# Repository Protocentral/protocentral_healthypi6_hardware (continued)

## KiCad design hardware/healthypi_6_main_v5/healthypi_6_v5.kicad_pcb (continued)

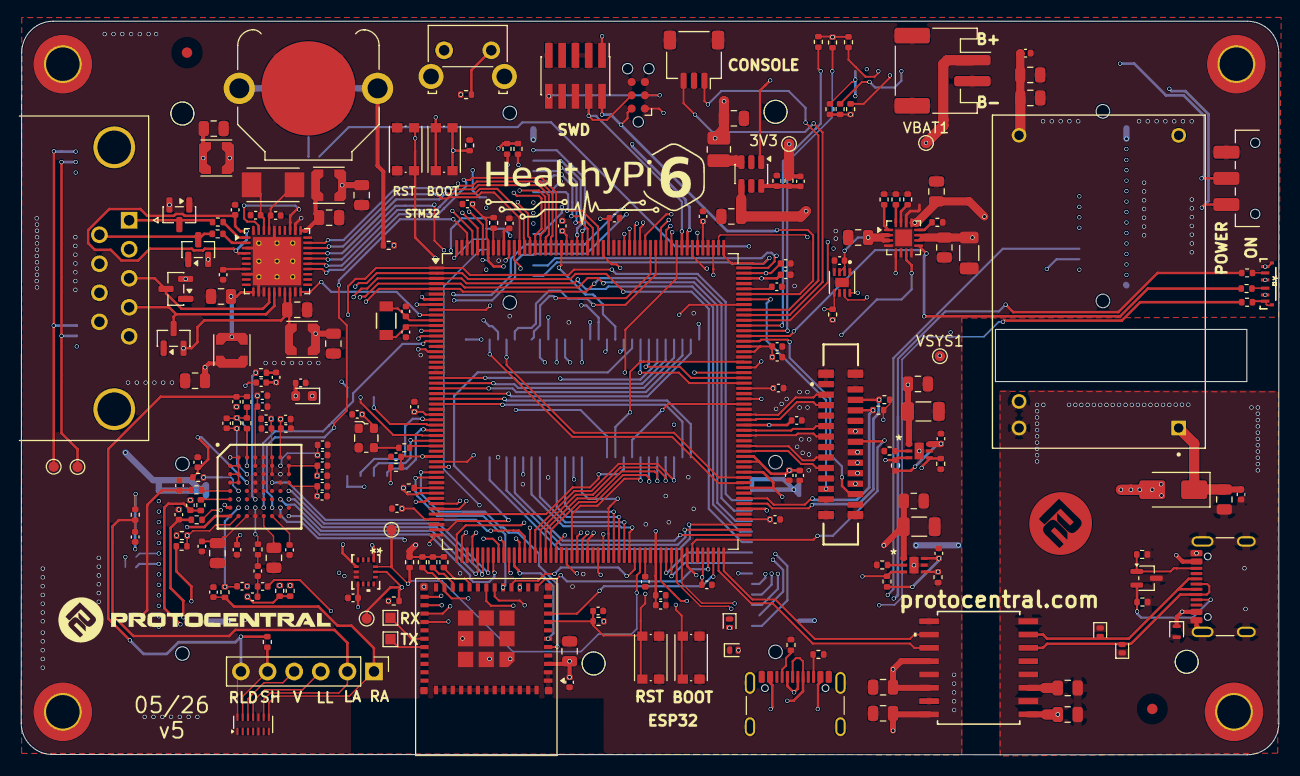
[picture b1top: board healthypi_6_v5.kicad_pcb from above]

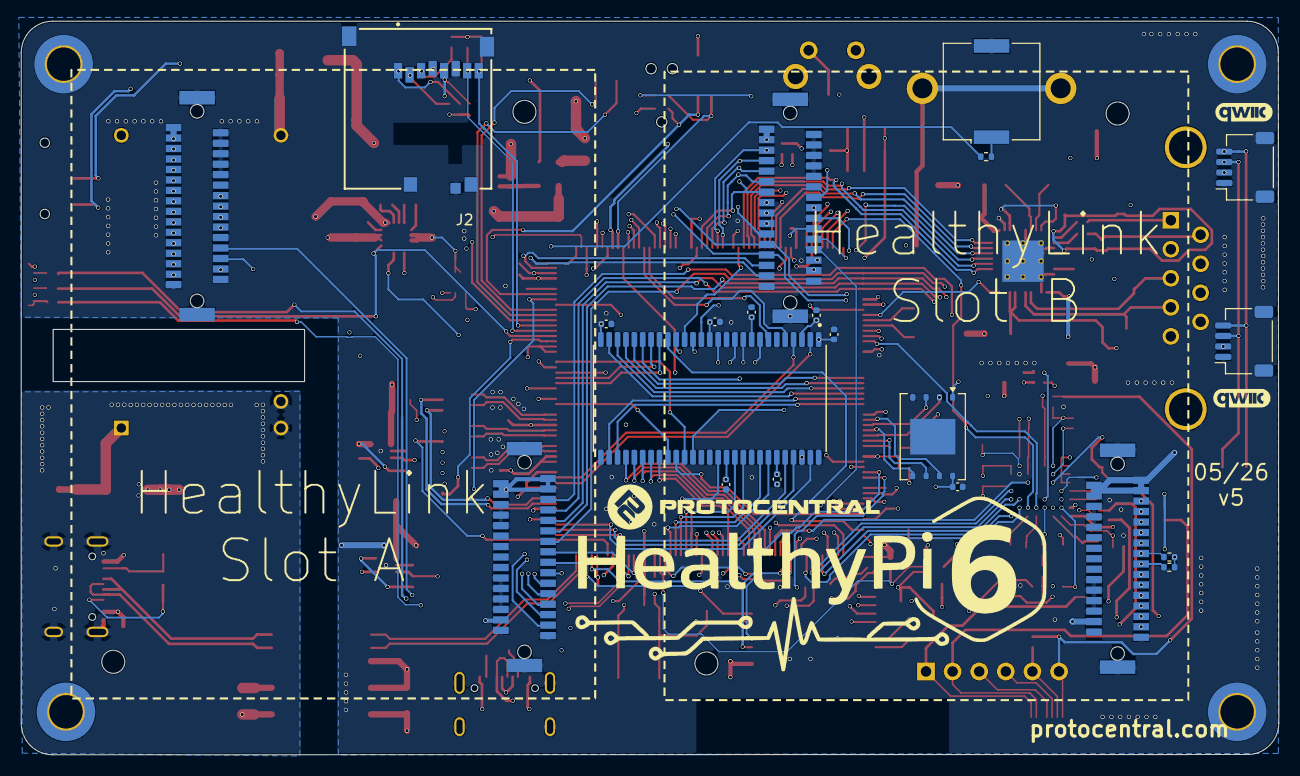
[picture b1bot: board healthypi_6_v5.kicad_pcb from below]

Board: 6 copper layers, 120.0 x 70.0 mm, 240 parts (17 on the bottom side), 241 nets.

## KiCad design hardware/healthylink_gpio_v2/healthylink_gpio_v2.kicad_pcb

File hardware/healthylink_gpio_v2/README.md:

# HealthyLink GPIO Module

| | |
|---|---|
| Revision | **v2** |
| Role | HealthyLink GPIO breakout — the minimal module example |
| Board | 50 × 62.2 mm, 2-layer |
| Slot | Occupies one HealthyLink slot (J5) |
| KiCad | 10 |
| Schematic PDF | [`healthylink-gpio-v2-schematic.pdf`](healthylink-gpio-v2-schematic.pdf) |

## Files

| File | Contents |
|---|---|
| `healthylink_gpio_v2.kicad_pro` / `.kicad_sch` / `.kicad_pcb` | KiCad project for this revision |
| `healthylink-gpio-v2-schematic.pdf` | Exported schematic — the human-readable reference |

## What it does

A single-sheet board that brings the HealthyLink bus out to two 2×10 headers. It is the
smallest complete module in this repository and the recommended starting point for your
own design: it shows the three things every module needs and nothing else.

- **Connector** — one `HEALTHYLINK_DF9_DUAL` (J5), the two DF9-31 receptacles of one slot
- **Identification** — AT24CS02 EEPROM on `I2C3`, with a write-protect solder jumper
- **Power** — a TPS62A02 buck off the module rail

Both SPI buses, `I2C3`, `USART2`, the six analog inputs, CAN, the stacking bus and the
per-slot interrupt and reset all reach the headers. See
[`docs/HEALTHYLINK.md`](../../docs/HEALTHYLINK.md) for the pinout.

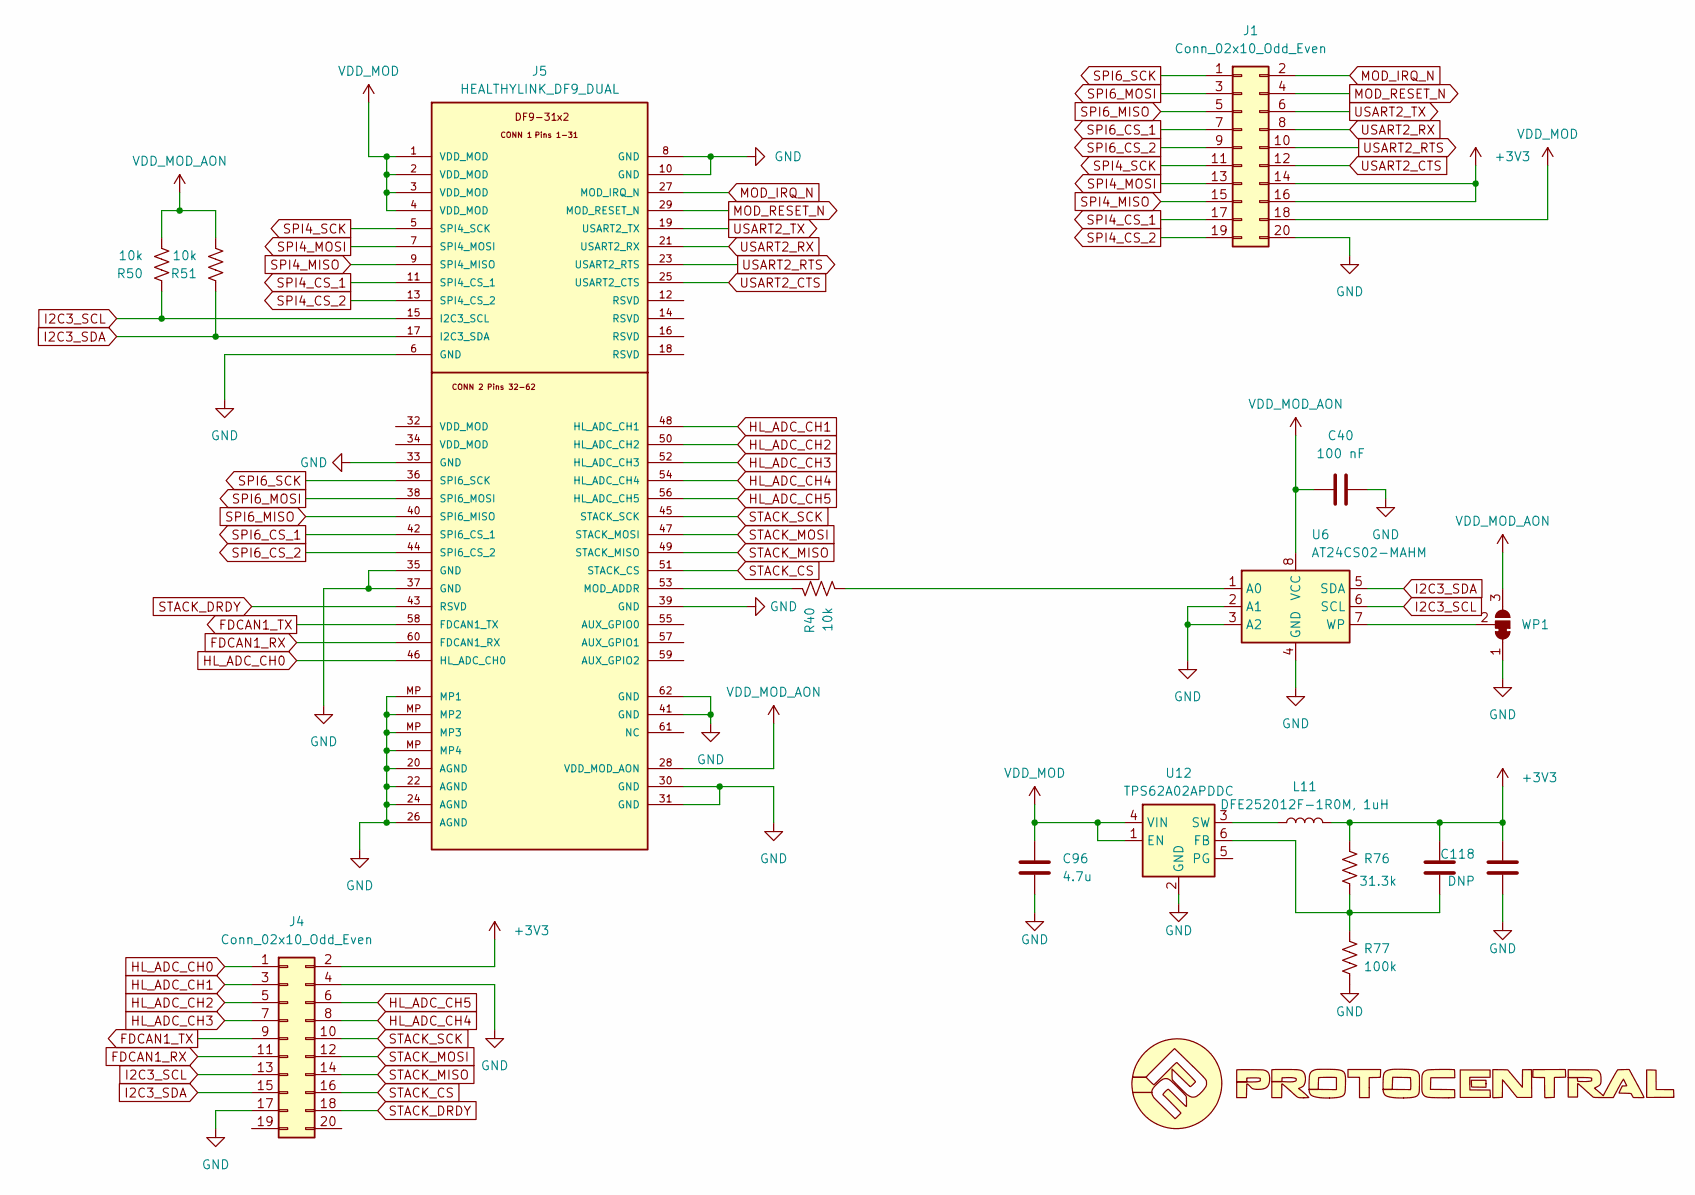
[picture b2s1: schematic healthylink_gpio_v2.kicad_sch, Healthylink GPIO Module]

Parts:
C40: 100 nF; C_0402_1005Metric
C96: 4.7u; C_0805_2012Metric
C118: DNP; C_0402_1005Metric
C119: 22u; C_0805_2012Metric
J1, J4: Conn_02x10_Odd_Even; PinSocket_2x10_P2.54mm_Horizontal
J5: HEALTHYLINK_DF9_DUAL; healthylink_df9_module
L11: DFE252012F-1R0M, 1uH; L_1008_2520Metric
R40, R50, R51: 10k; R_0402_1005Metric
R76: 31.3k; R_0402_1005Metric
R77: 100k; R_0402_1005Metric
U4: LOGO
U6: AT24CS02-MAHM; DFN-8-1EP_3x2mm_P0.5mm_EP1.3x1.5mm
U12: TPS62A02APDDC; SOT-23-6
WP1: SolderJumper_3_Bridged12; SolderJumper-3_P1.3mm_Bridged12_RoundedPad1.0x1.5mm

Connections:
+3V3: C118.2, C119.1, J1.14, J1.16, J4.2, L11.2, R76.2
FDCAN1_RX: J4.11, J5.60 (FDCAN1_RX)
FDCAN1_TX: J4.9, J5.58 (FDCAN1_TX)
GND: C40.1, C96.2, C119.2, J1.20, J4.4, J4.17, J5.6 (GND), J5.8 (GND), J5.10 (GND), J5.20 (AGND), J5.22 (AGND), J5.24 (AGND), J5.26 (AGND), J5.30 (GND), J5.31 (GND), J5.33 (GND), J5.35 (GND), J5.37 (GND), J5.39 (GND), J5.41 (GND), J5.62 (GND), J5.MP (MP1), R77.1, U6.2 (A1), U6.3 (A2), U6.4 (GND), U6.9 (GND), U12.2 (GND), WP1.1 (A)
HL_ADC_CH0: J4.1, J5.46 (HL_ADC_CH0)
HL_ADC_CH1: J4.3, J5.48 (HL_ADC_CH1)
HL_ADC_CH2: J4.5, J5.50 (HL_ADC_CH2)
HL_ADC_CH3: J4.7, J5.52 (HL_ADC_CH3)
HL_ADC_CH4: J4.8, J5.54 (HL_ADC_CH4)
HL_ADC_CH5: J4.6, J5.56 (HL_ADC_CH5)
I2C3_SCL: J4.13, J5.15 (I2C3_SCL), R50.1, U6.6 (SCL)
I2C3_SDA: J4.15, J5.17 (I2C3_SDA), R51.1, U6.5 (SDA)
MOD_IRQ_N: J1.2, J5.27 (MOD_IRQ_N)
MOD_RESET_N: J1.4, J5.29 (MOD_RESET_N)
unnamed: J5.53 (MOD_ADDR), R40.1
unnamed: R40.2, U6.1 (A0)
unnamed: U6.7 (WP), WP1.2 (C)
unnamed: C118.1, R76.1, R77.2, U12.6 (FB)
unnamed: L11.1, U12.3 (SW)
SPI4_CS_1: J1.17, J5.11 (SPI4_CS_1)
SPI4_CS_2: J1.19, J5.13 (SPI4_CS_2)
SPI4_MISO: J1.15, J5.9 (SPI4_MISO)
SPI4_MOSI: J1.13, J5.7 (SPI4_MOSI)
SPI4_SCK: J1.11, J5.5 (SPI4_SCK)
SPI6_CS_1: J1.7, J5.42 (SPI6_CS_1)
SPI6_CS_2: J1.9, J5.44 (SPI6_CS_2)
SPI6_MISO: J1.5, J5.40 (SPI6_MISO)
SPI6_MOSI: J1.3, J5.38 (SPI6_MOSI)
SPI6_SCK: J1.1, J5.36 (SPI6_SCK)
STACK_CS: J4.16, J5.51 (STACK_CS)
STACK_DRDY: J4.18, J5.43 (RSVD)
STACK_MISO: J4.14, J5.49 (STACK_MISO)
STACK_MOSI: J4.12, J5.47 (STACK_MOSI)
STACK_SCK: J4.10, J5.45 (STACK_SCK)
USART2_CTS: J1.12, J5.25 (USART2_CTS)
USART2_RTS: J1.10, J5.23 (USART2_RTS)
USART2_RX: J1.8, J5.21 (USART2_RX)
USART2_TX: J1.6, J5.19 (USART2_TX)
VDD_MOD: C96.1, J1.18, J5.1 (VDD_MOD), J5.2 (VDD_MOD), J5.3 (VDD_MOD), J5.4 (VDD_MOD), U12.1 (EN), U12.4 (VIN)
VDD_MOD_AON: C40.2, J5.28 (VDD_MOD_AON), R50.2, R51.2, U6.8 (VCC), WP1.3 (B)

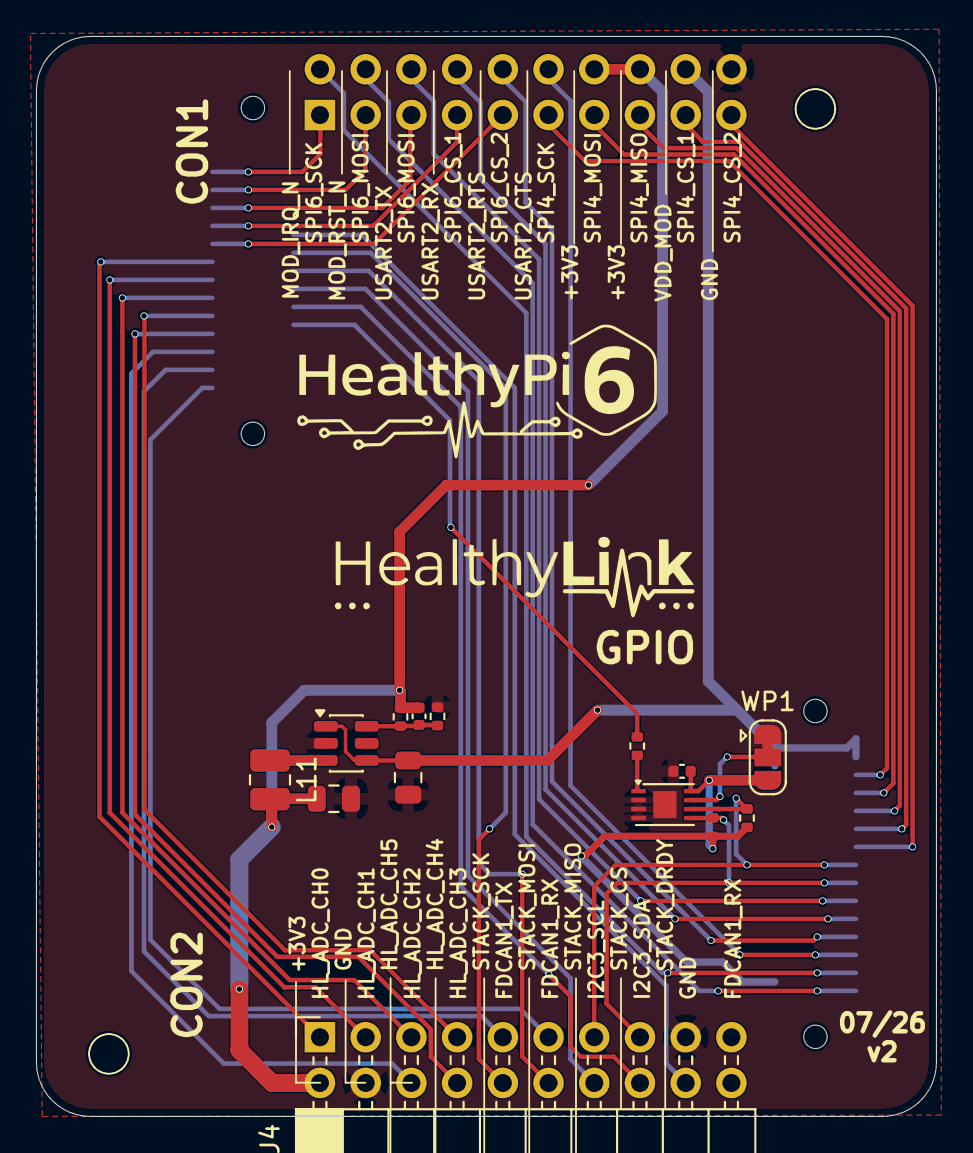
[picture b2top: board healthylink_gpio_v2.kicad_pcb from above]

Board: 2 copper layers, 50.0 x 60.0 mm, 16 parts (1 on the bottom side), 40 nets.

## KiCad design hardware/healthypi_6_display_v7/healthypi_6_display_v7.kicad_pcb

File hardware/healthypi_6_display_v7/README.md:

# HealthyPi 6 Display Board

| | |
|---|---|
| Revision | **v7** |
| Role | Display interface — routes MIPI-DSI and touch I²C from the main board to the 4" panel, and drives the backlight |
| Board | 60 × 33 mm, 2-layer |
| KiCad | 10 |
| Schematic PDF | [`healthypi6-display-v7-schematic.pdf`](healthypi6-display-v7-schematic.pdf) |

## Files

| File | Contents |
|---|---|
| `healthypi_6_display_v7.kicad_pro` / `.kicad_sch` / `.kicad_pcb` | KiCad project for this revision |
| `healthypi6-display-v7-schematic.pdf` | Exported schematic — the human-readable reference |

## Interfaces

- 24-way FFC to the main board: 2-lane MIPI-DSI, touch I²C (`TP_SCL` / `TP_SDA`,
  `TP_INT`, `TP_RST`), panel reset and tearing-effect (`MIPI_RST`, `MIPI_TE`)
- TPS61158 boost driving the panel backlight, enabled by `MIPI_BKL`
- 12-way connector to the display panel

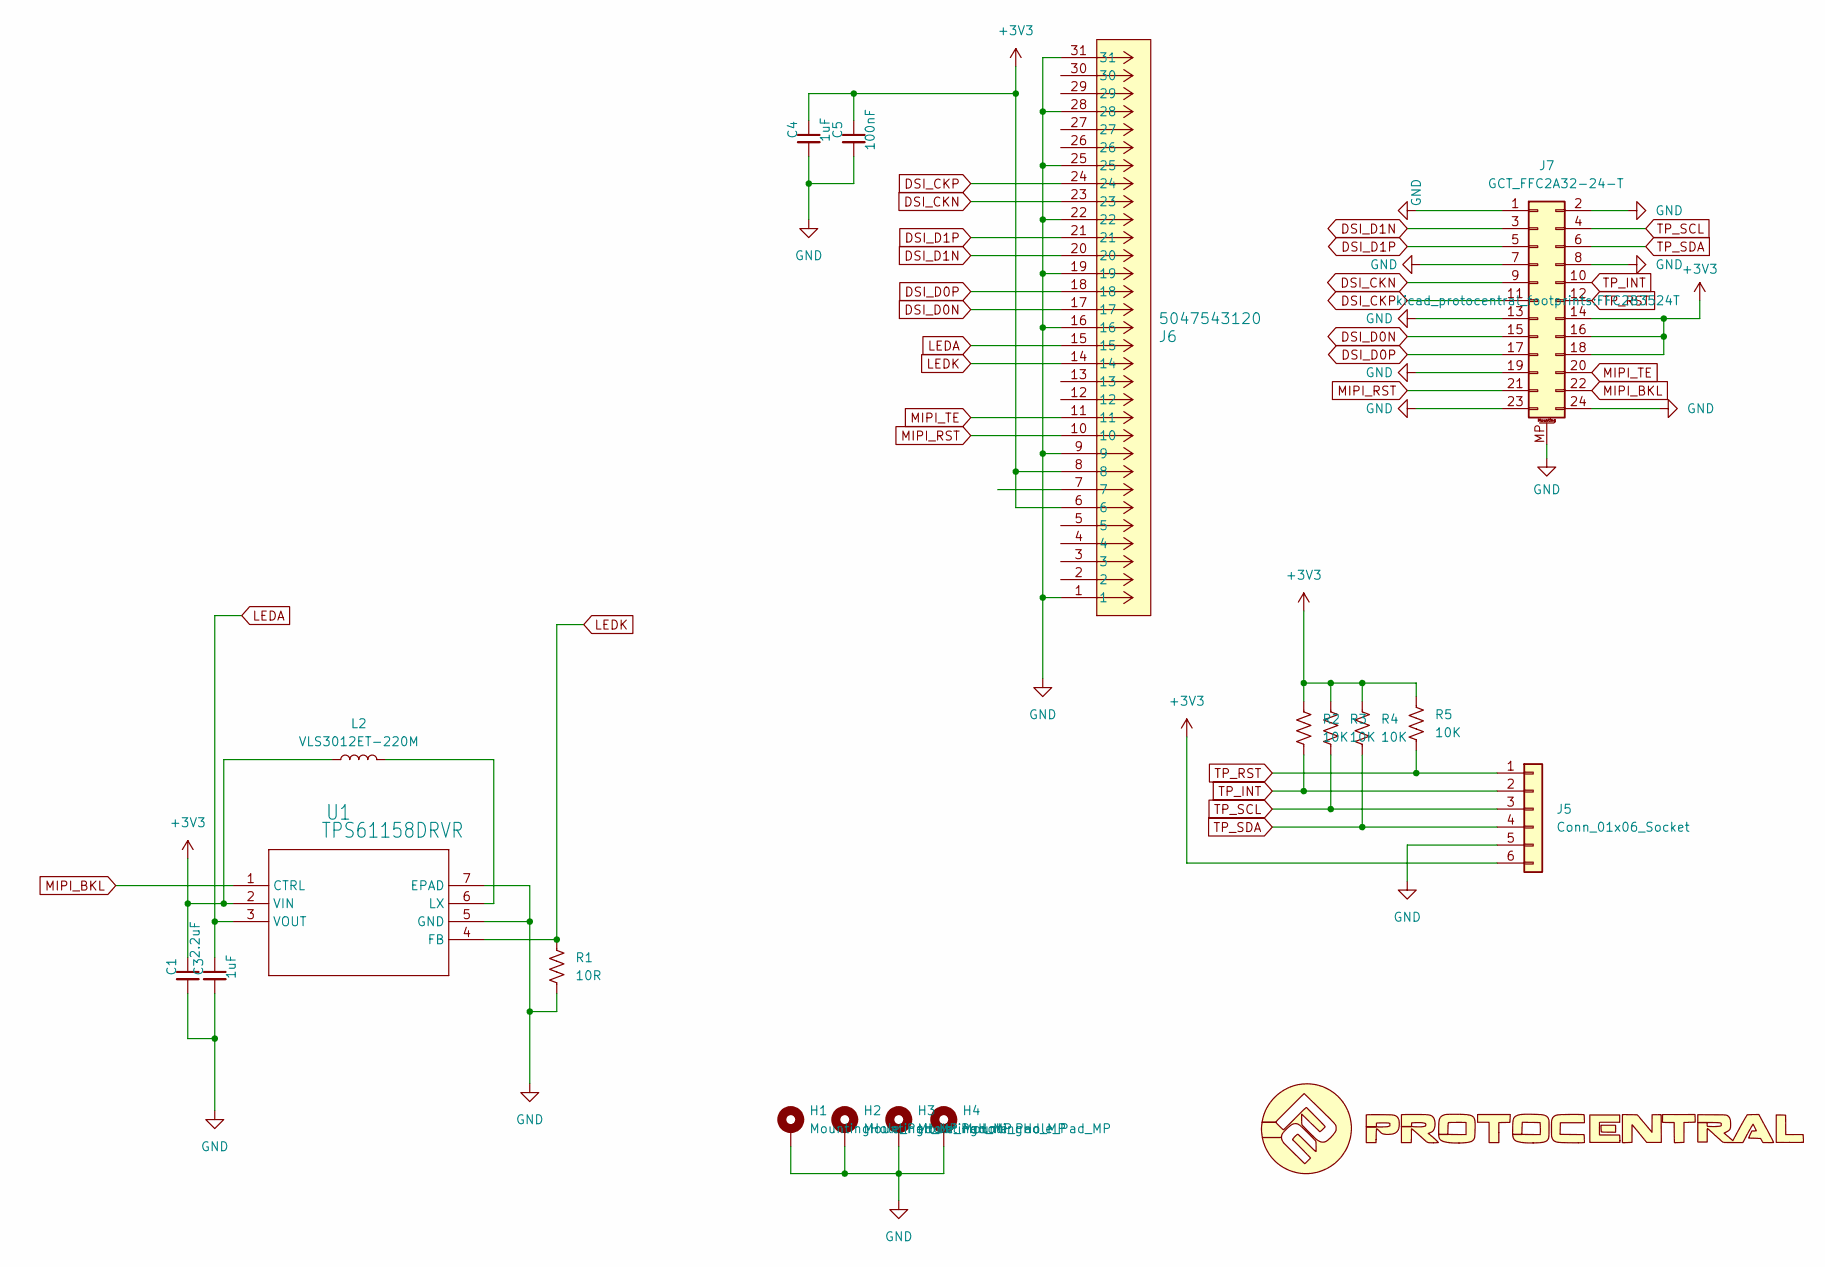
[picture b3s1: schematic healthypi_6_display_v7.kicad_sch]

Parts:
C1: 2.2uF; C_0402_1005Metric
C3, C4: 1uF; C_0402_1005Metric
C5: 100nF; C_0402_1005Metric
H1: MountingHole_Pad_MP; MountingHole_3.2mm_M3_Pad
H2, H3, H4: MountingHole_Pad_MP; MountingHole_3.2mm_M3_ISO14580_Pad
J5: Conn_01x06_Socket; TE_2328702-6
J6: 5047543120; TE_3-2328724-1
J7: GCT_FFC2A32-24-T; FFC2B3524T
L2: VLS3012ET-220M; L_Sunlord_SWPA3012S
R1: 10R; R_0402_1005Metric
R2, R3, R4, R5: 10K; R_0402_1005Metric
U1: TPS61158DRVR; DRV6_1P6X1_TEX_38825256
U2: LOGO

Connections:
+3V3: C1.1, C4.1, C5.1, J5.6, J6.6, J6.8, J7.14, J7.16, J7.18, L2.1, R2.1, R3.1, R4.1, R5.1, U1.2 (VIN)
DSI_CKN: J6.23, J7.9
DSI_CKP: J6.24, J7.11
DSI_D0N: J6.17, J7.15
DSI_D0P: J6.18, J7.17
DSI_D1N: J6.20, J7.3
DSI_D1P: J6.21, J7.5
GND: C1.2, C3.2, C4.2, C5.2, H1.1 (1_1), H2.1 (1_1), H3.1 (1_1), H4.1 (1_1), J5.5, J6.1, J6.9, J6.16, J6.19, J6.22, J6.25, J6.28, J6.31, J7.1, J7.2, J7.7, J7.8, J7.13, J7.19, J7.23, J7.24, J7.MP (MountPin), R1.2, U1.5 (GND), U1.7 (EPAD)
LEDA: C3.1, J6.15, U1.3 (VOUT)
LEDK: J6.14, R1.1, U1.4 (FB)
MIPI_BKL: J7.22, U1.1 (CTRL)
MIPI_RST: J6.10, J7.21
MIPI_TE: J6.11, J7.20
unnamed: L2.2, U1.6 (LX)
TP_INT: J5.2, J7.10, R2.2
TP_RST: J5.1, J7.12, R5.2
TP_SCL: J5.3, J7.4, R3.2
TP_SDA: J5.4, J7.6, R4.2

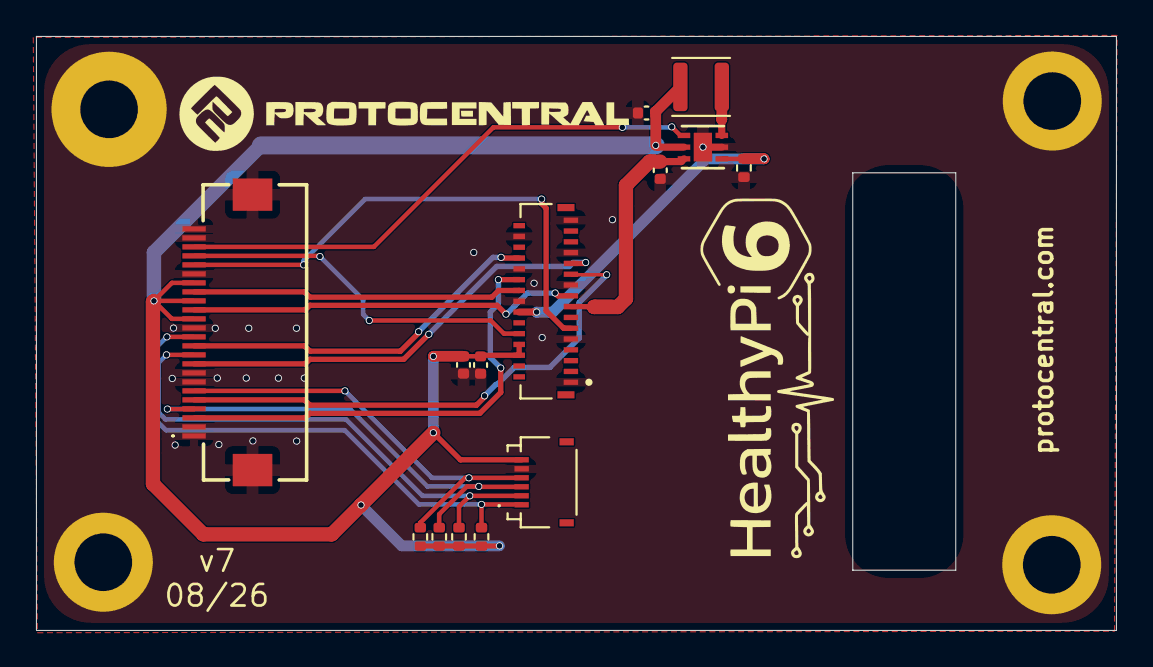
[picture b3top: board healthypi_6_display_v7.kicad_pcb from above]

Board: 2 copper layers, 60.0 x 33.0 mm, 18 parts (0 on the bottom side), 18 nets.

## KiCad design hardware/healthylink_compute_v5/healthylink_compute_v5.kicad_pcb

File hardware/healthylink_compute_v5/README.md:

# HealthyLink Compute Module

| | |
|---|---|
| Revision | **v5** |
| Role | HealthyLink compute / NPU module — STM32N657 with camera and storage |
| Board | 50 × 60 mm, 6-layer |
| Slot | Occupies one HealthyLink slot (J5) |
| KiCad | 10 |
| Schematic PDF | [`healthylink-compute-v5-schematic.pdf`](healthylink-compute-v5-schematic.pdf) |

## Files

| File | Contents |
|---|---|
| `healthylink_compute_v5.kicad_pro` / `.kicad_sch` / `.kicad_pcb` | KiCad project for this revision |
| `healthylink-compute-v5-schematic.pdf` | Exported schematic — the human-readable reference |

## Schematic sheets

Sheet names and filenames do not line up on this project; the table gives both.

| Sheet | File | Contents |
|---|---|---|
| *(root)* | `healthylink_compute_v5.kicad_sch` | HealthyLink connector, AT24CS02 ID EEPROM, write-protect jumper |
| MCU | `mcu.kicad_sch` | STM32N657I0H3Q, MX25UM51245G octal flash, boot configuration, 32.768 kHz |
| MCU2 | `mcu2.kicad_sch` | 48 MHz oscillator, status LEDs, debug header |
| MCU3 | `power.kicad_sch` | STM32N657 power pins and decoupling |
| power | `sys_power.kicad_sch` | TPS2116 power mux, 3 × TPS62A02 bucks, TLV75518 LDO |
| connectivity | `connectivity.kicad_sch` | microSD, USB-C, MIPI-CSI camera header |

## Bus usage

Of the HealthyLink signals, this module uses `SPI4` (`CS_1`), `I2C3`, `USART2`,
`MOD_IRQ_N`, `MOD_RESET_N` and the stacking bus. See
[`docs/HEALTHYLINK.md`](../../docs/HEALTHYLINK.md) for the full pinout.

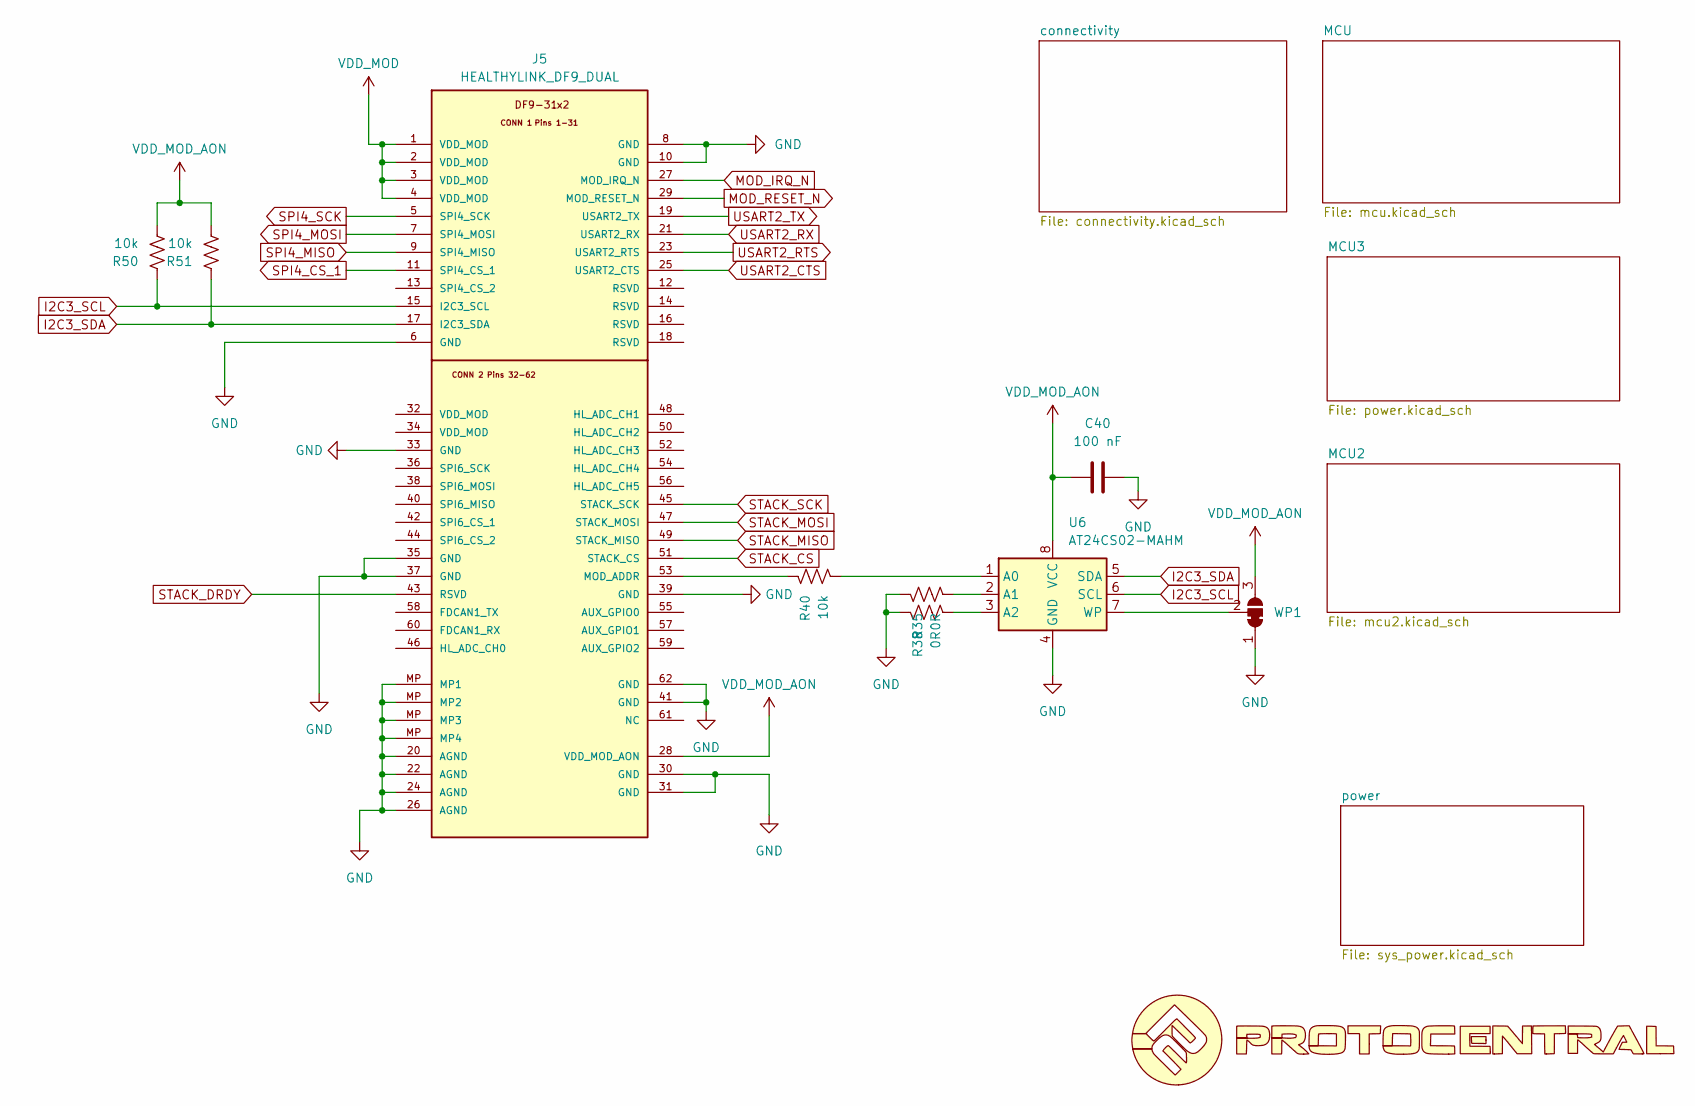
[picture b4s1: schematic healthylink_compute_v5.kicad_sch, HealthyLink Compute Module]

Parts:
C40: 100 nF; C_0402_1005Metric
J5: HEALTHYLINK_DF9_DUAL; healthylink_df9_module
R35, R38: 0R; R_0402_1005Metric
R40, R50, R51: 10k; R_0402_1005Metric
U6: AT24CS02-MAHM; DFN-8-1EP_3x2mm_P0.5mm_EP1.3x1.5mm
U18: LOGO
WP1: SolderJumper_3_Bridged12; SolderJumper-3_P1.3mm_Bridged12_RoundedPad1.0x1.5mm

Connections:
GND: C40.1, J5.6 (GND), J5.8 (GND), J5.10 (GND), J5.20 (AGND), J5.22 (AGND), J5.24 (AGND), J5.26 (AGND), J5.30 (GND), J5.31 (GND), J5.33 (GND), J5.35 (GND), J5.37 (GND), J5.39 (GND), J5.41 (GND), J5.62 (GND), J5.MP (MP3), R35.1, R38.1, U6.4 (GND), U6.9 (GND), WP1.1 (A); also elsewhere on the board
I2C3_SCL: J5.15 (I2C3_SCL), R50.1, U6.6 (SCL)
I2C3_SDA: J5.17 (I2C3_SDA), R51.1, U6.5 (SDA)
MOD_IRQ_N: J5.27 (MOD_IRQ_N); also elsewhere on the board
MOD_RESET_N: J5.29 (MOD_RESET_N); also elsewhere on the board
N6_SPI5_MISO: J5.9 (SPI4_MISO); also elsewhere on the board
N6_SPI5_MOSI: J5.7 (SPI4_MOSI); also elsewhere on the board
N6_SPI5_NSS: J5.11 (SPI4_CS_1); also elsewhere on the board
N6_SPI5_SCK: J5.5 (SPI4_SCK); also elsewhere on the board
N6_USART1_CTS: J5.23 (USART2_RTS); also elsewhere on the board
N6_USART1_RTS: J5.25 (USART2_CTS); also elsewhere on the board
N6_USART1_RX: J5.19 (USART2_TX); also elsewhere on the board
N6_USART1_TX: J5.21 (USART2_RX); also elsewhere on the board
unnamed: J5.53 (MOD_ADDR), R40.1
unnamed: R40.2, U6.1 (A0)
unnamed: R35.2, U6.2 (A1)
unnamed: R38.2, U6.3 (A2)
unnamed: U6.7 (WP), WP1.2 (C)
STACK_CS: J5.51 (STACK_CS); also elsewhere on the board
STACK_DRDY: J5.43 (RSVD); also elsewhere on the board
STACK_MISO: J5.49 (STACK_MISO); also elsewhere on the board
STACK_MOSI: J5.47 (STACK_MOSI); also elsewhere on the board
STACK_SCK: J5.45 (STACK_SCK); also elsewhere on the board
VDD_MOD: J5.1 (VDD_MOD), J5.2 (VDD_MOD), J5.3 (VDD_MOD), J5.4 (VDD_MOD); also elsewhere on the board
VDD_MOD_AON: C40.2, J5.28 (VDD_MOD_AON), R50.2, R51.2, U6.8 (VCC), WP1.3 (B)

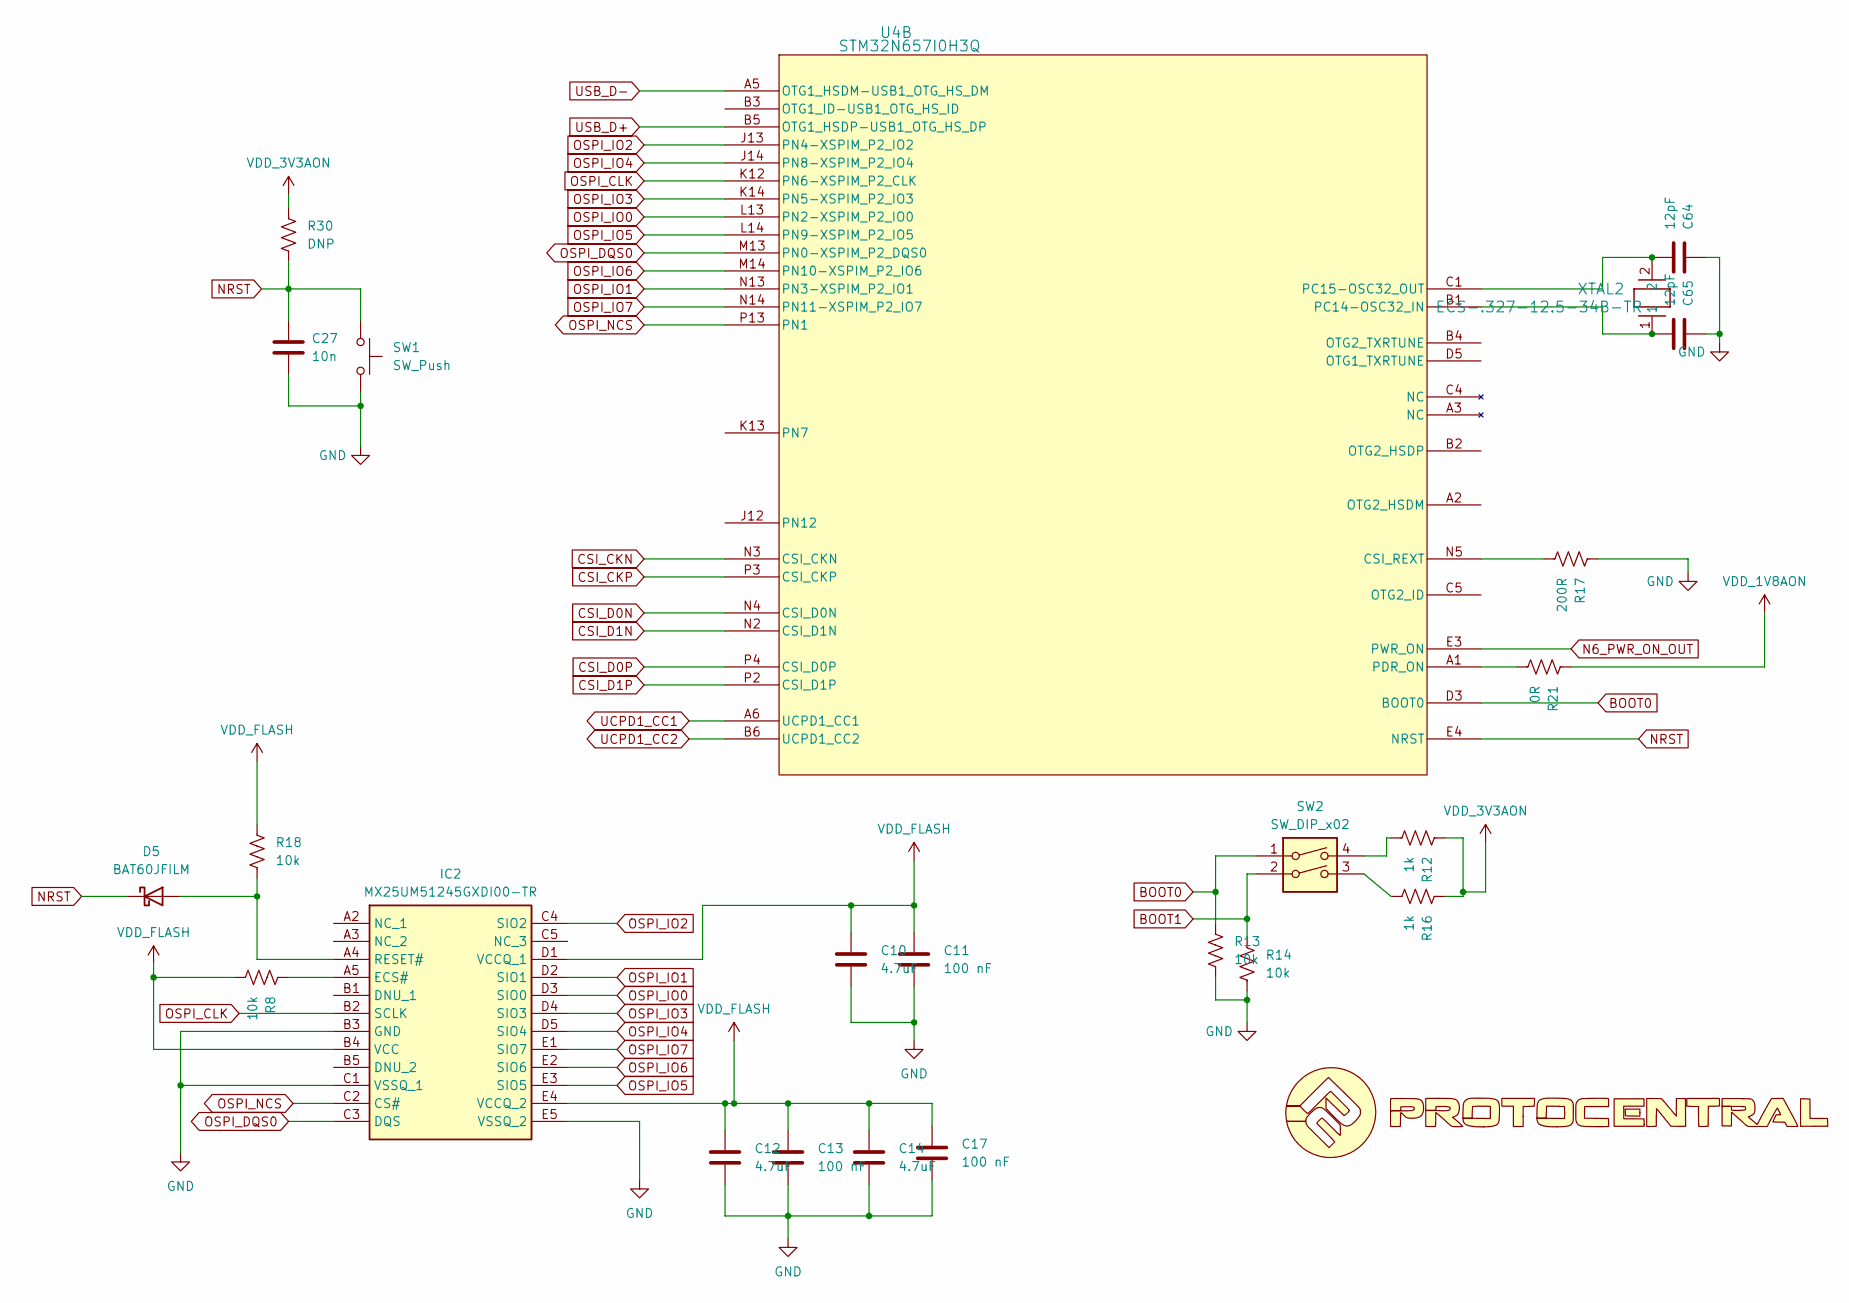
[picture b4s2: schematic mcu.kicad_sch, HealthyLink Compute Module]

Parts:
C10, C12, C14: 4.7uF; C_0805_2012Metric
C11, C13, C17: 100 nF; C_0402_1005Metric
C27: 10n; C_0402_1005Metric
C64, C65: 12pF; C_0402_1005Metric
D5: BAT60JFILM; D_SOD-323
IC2: MX25UM51245GXDI00-TR; BGA24C100P5X5_600X800X120; Mouser Part Number 95-25UM51245GXDITR
R8, R13, R14, R18: 10k; R_0402_1005Metric
R12, R16: 1k; R_0402_1005Metric
R17: 200R; R_0402_1005Metric
R21: 0R; R_0402_1005Metric
R30: DNP; R_0402_1005Metric
SW1: SW_Push; SW_Push_1P1T_NO_CK_KMR2
SW2: SW_DIP_x02; SW_DS04-254-2-02BK-SMT
U4: STM32N657I0H3Q; VFBGA178_12X12_STM
U23: LOGO
XTAL2: ECS-.327-12.5-34B-TR; Crystal_SMD_MicroCrystal_CC8V-T1A-2Pin_2.0x1.2mm_HandSolder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

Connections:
BOOT0: R13.1, SW2.1, U4.D3 (BOOT0)
BOOT1: R14.1, SW2.2; also elsewhere on the board
CSI_CKN: U4.N3 (CSI_CKN); also elsewhere on the board
CSI_CKP: U4.P3 (CSI_CKP); also elsewhere on the board
CSI_D0N: U4.N4 (CSI_D0N); also elsewhere on the board
CSI_D0P: U4.P4 (CSI_D0P); also elsewhere on the board
CSI_D1N: U4.N2 (CSI_D1N); also elsewhere on the board
CSI_D1P: U4.P2 (CSI_D1P); also elsewhere on the board
GND: C10.2, C11.2, C12.2, C13.2, C14.2, C17.2, C27.2, C64.1, C65.1, IC2.B3 (GND), IC2.C1 (VSSQ_1), IC2.E5 (VSSQ_2), R13.2, R14.2, R17.1, SW1.2; also elsewhere on the board
N6_PWR_ON_OUT: U4.E3 (PWR_ON); also elsewhere on the board
NRST: C27.1, D5.1 (K), R30.2, SW1.1, U4.E4 (NRST); also elsewhere on the board
unnamed: D5.2 (A), IC2.A4 (RESET#), R18.2
unnamed: IC2.A5 (ECS#), R8.1
unnamed: R12.2, SW2.4
unnamed: R16.2, SW2.3
unnamed: R17.2, U4.N5 (CSI_REXT)
unnamed: C65.2, U4.B1 (PC14-OSC32_IN), XTAL2.1
unnamed: C64.2, U4.C1 (PC15-OSC32_OUT), XTAL2.2
unnamed: R21.2, U4.A1 (PDR_ON)
OSPI_CLK: IC2.B2 (SCLK), U4.K12 (PN6-XSPIM_P2_CLK)
OSPI_DQS0: IC2.C3 (DQS), U4.M13 (PN0-XSPIM_P2_DQS0)
OSPI_IO0: IC2.D3 (SIO0), U4.L13 (PN2-XSPIM_P2_IO0)
OSPI_IO1: IC2.D2 (SIO1), U4.N13 (PN3-XSPIM_P2_IO1)
OSPI_IO2: IC2.C4 (SIO2), U4.J13 (PN4-XSPIM_P2_IO2)
OSPI_IO3: IC2.D4 (SIO3), U4.K14 (PN5-XSPIM_P2_IO3)
OSPI_IO4: IC2.D5 (SIO4), U4.J14 (PN8-XSPIM_P2_IO4)
OSPI_IO5: IC2.E3 (SIO5), U4.L14 (PN9-XSPIM_P2_IO5)
OSPI_IO6: IC2.E2 (SIO6), U4.M14 (PN10-XSPIM_P2_IO6)
OSPI_IO7: IC2.E1 (SIO7), U4.N14 (PN11-XSPIM_P2_IO7)
OSPI_NCS: IC2.C2 (CS#), U4.P13 (PN1)
UCPD1_CC1: U4.A6 (UCPD1_CC1)
UCPD1_CC2: U4.B6 (UCPD1_CC2)
USB_D+: U4.B5 (OTG1_HSDP-USB1_OTG_HS_DP); also elsewhere on the board
USB_D-: U4.A5 (OTG1_HSDM-USB1_OTG_HS_DM); also elsewhere on the board
VDD_1V8AON: R21.1; also elsewhere on the board
VDD_3V3AON: R12.1, R16.1, R30.1; also elsewhere on the board
VDD_FLASH: C10.1, C11.1, C12.1, C13.1, C14.1, C17.1, IC2.B4 (VCC), IC2.D1 (VCCQ_1), IC2.E4 (VCCQ_2), R8.2, R18.1; also elsewhere on the board

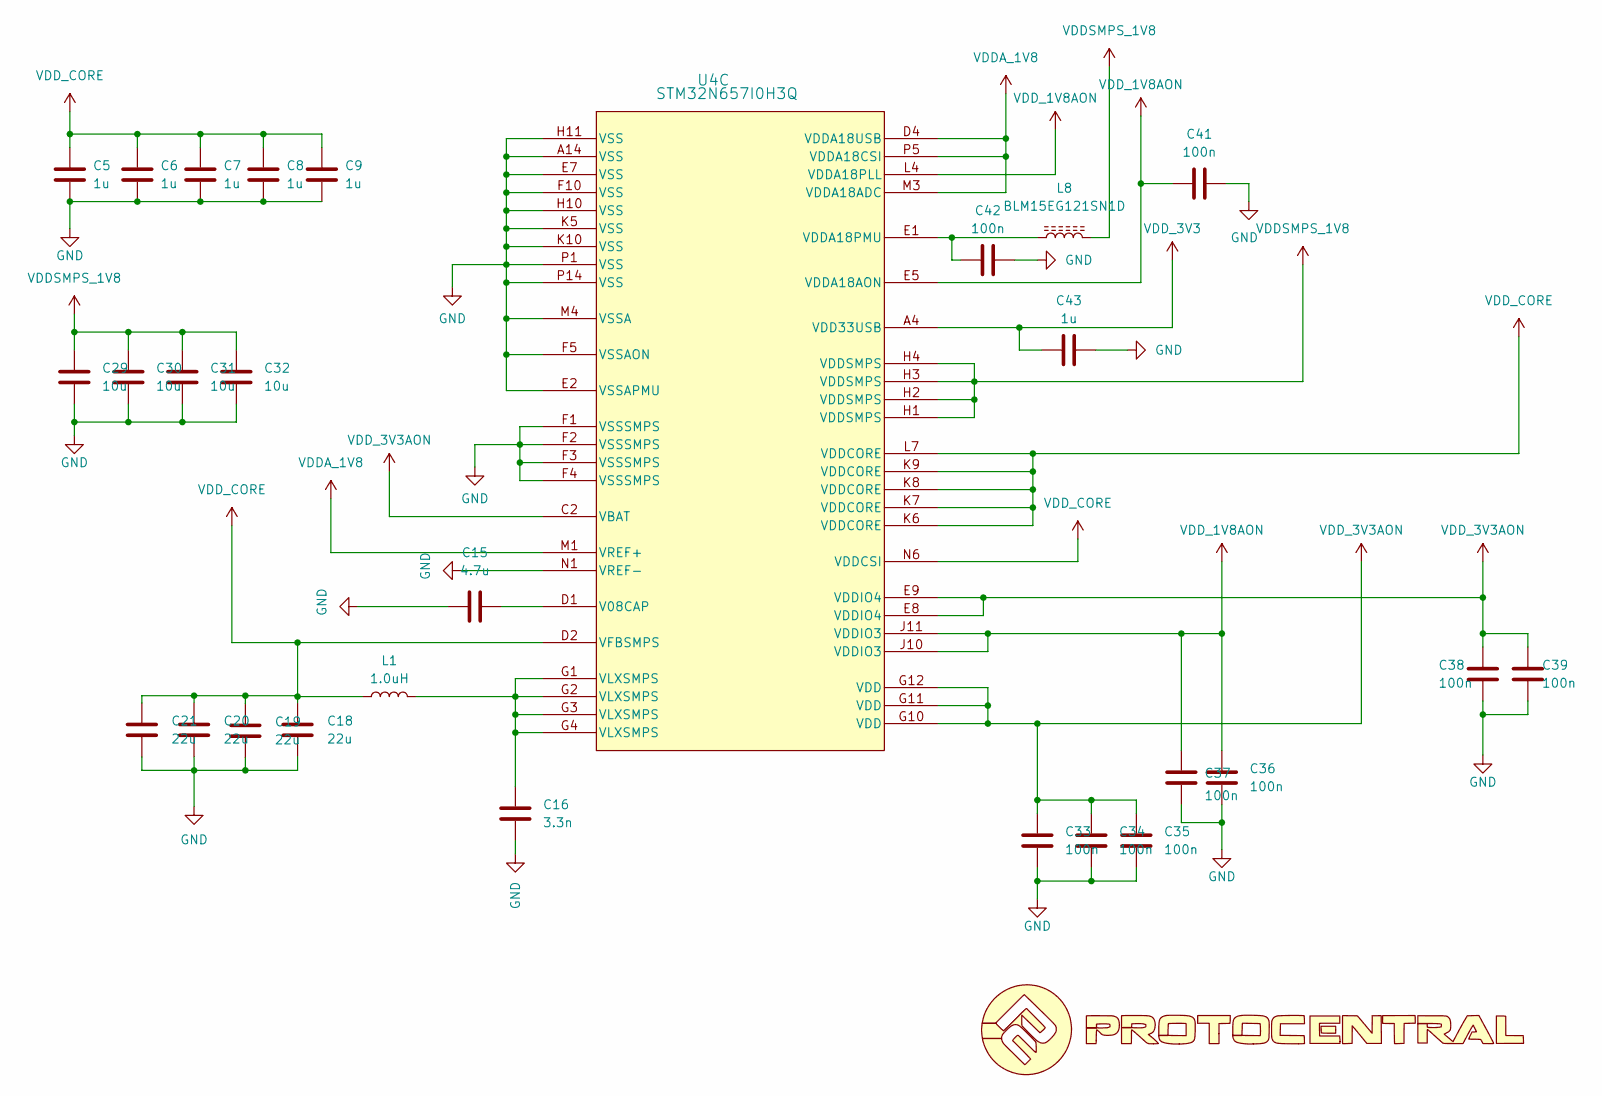
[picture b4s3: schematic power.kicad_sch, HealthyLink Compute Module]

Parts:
C5, C6, C7, C8, C9, C43: 1u; C_0402_1005Metric
C15: 4.7u; C_0402_1005Metric
C16: 3.3n; C_0402_1005Metric
C18, C19, C20, C21: 22u; C_0805_2012Metric
C29, C30, C31, C32: 10u; C_0402_1005Metric
C33, C34, C35, C36, C37, C38, C39, C41, C42: 100n; C_0402_1005Metric
L1: 1.0uH; L_1206_3216Metric
L8: BLM15EG121SN1D; L_0402_1005Metric
U4: STM32N657I0H3Q; VFBGA178_12X12_STM
U22: LOGO

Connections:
GND: C5.2, C6.2, C7.2, C8.2, C9.2, C15.1, C16.1, C18.1, C19.1, C20.1, C21.1, C29.2, C30.2, C31.2, C32.2, C33.2, C34.2, C35.2, C36.2, C37.2, C38.2, C39.2, C41.2, C42.2, C43.2, U4.A14 (VSS), U4.E2 (VSSAPMU), U4.E7 (VSS), U4.F1 (VSSSMPS), U4.F2 (VSSSMPS), U4.F3 (VSSSMPS), U4.F4 (VSSSMPS), U4.F5 (VSSAON), U4.F10 (VSS), U4.H10 (VSS), U4.H11 (VSS), U4.K5 (VSS), U4.K10 (VSS), U4.M4 (VSSA), U4.N1 (VREF-), U4.P1 (VSS), U4.P14 (VSS); also elsewhere on the board
unnamed: C16.2, L1.2, U4.G1 (VLXSMPS), U4.G2 (VLXSMPS), U4.G3 (VLXSMPS), U4.G4 (VLXSMPS)
unnamed: C15.2, U4.D1 (V08CAP)
unnamed: C42.1, L8.1, U4.E1 (VDDA18PMU)
VDDA_1V8: U4.D4 (VDDA18USB), U4.M1 (VREF+), U4.M3 (VDDA18ADC), U4.P5 (VDDA18CSI); also elsewhere on the board
VDDSMPS_1V8: C29.1, C30.1, C31.1, C32.1, L8.2, U4.H1 (VDDSMPS), U4.H2 (VDDSMPS), U4.H3 (VDDSMPS), U4.H4 (VDDSMPS); also elsewhere on the board
VDD_1V8AON: C36.1, C37.1, C41.1, U4.E5 (VDDA18AON), U4.J10 (VDDIO3), U4.J11 (VDDIO3), U4.L4 (VDDA18PLL); also elsewhere on the board
VDD_3V3: C43.1, U4.A4 (VDD33USB); also elsewhere on the board
VDD_3V3AON: C33.1, C34.1, C35.1, C38.1, C39.1, U4.C2 (VBAT), U4.E8 (VDDIO4), U4.E9 (VDDIO4), U4.G10 (VDD), U4.G11 (VDD), U4.G12 (VDD); also elsewhere on the board
VDD_CORE: C5.1, C6.1, C7.1, C8.1, C9.1, C18.2, C19.2, C20.2, C21.2, L1.1, U4.D2 (VFBSMPS), U4.K6 (VDDCORE), U4.K7 (VDDCORE), U4.K8 (VDDCORE), U4.K9 (VDDCORE), U4.L7 (VDDCORE), U4.N6 (VDDCSI)
